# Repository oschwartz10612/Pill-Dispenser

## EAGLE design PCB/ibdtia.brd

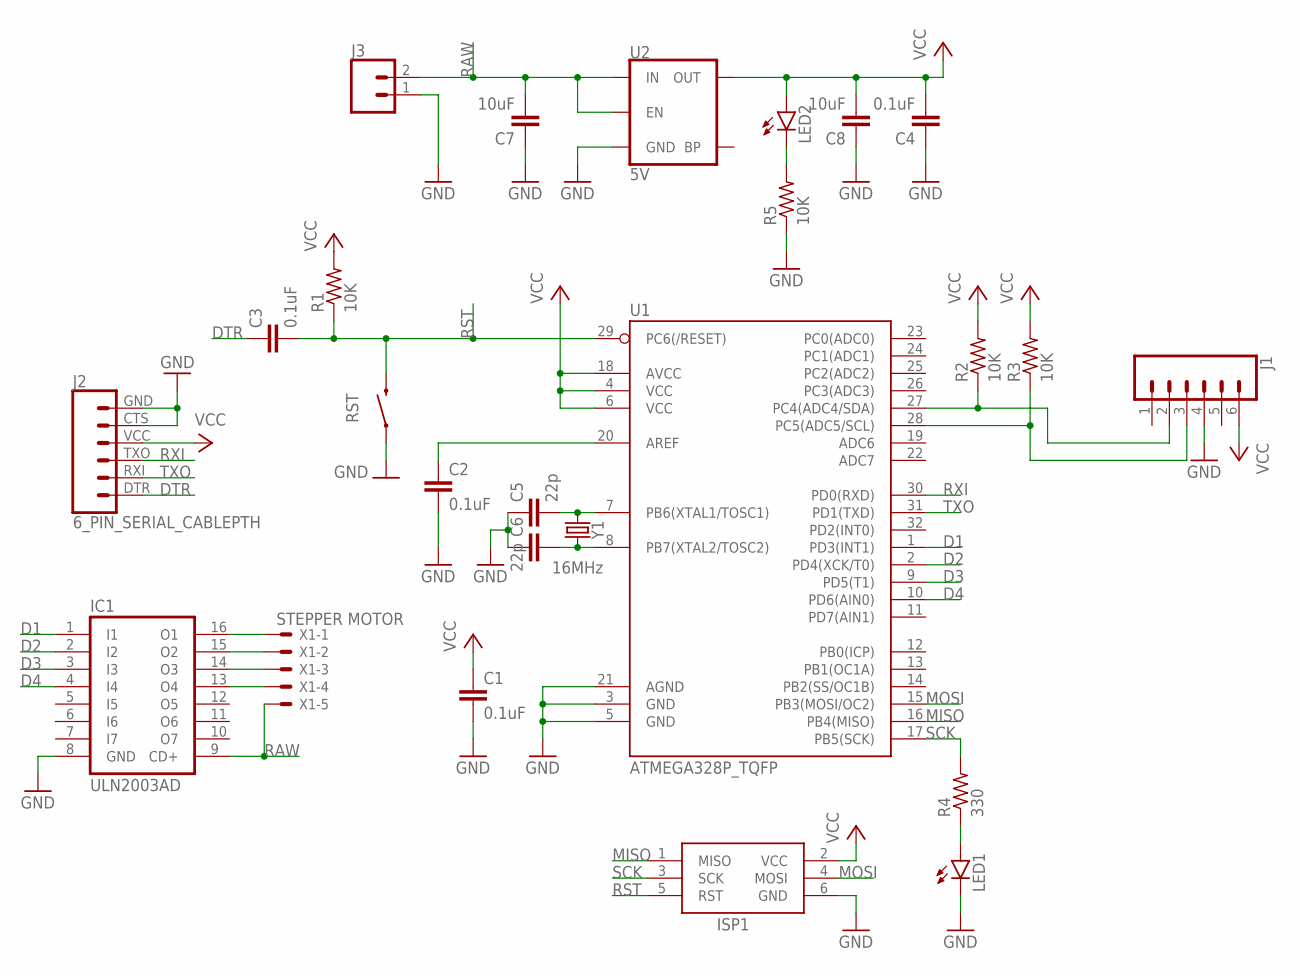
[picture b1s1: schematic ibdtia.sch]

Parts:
C1, C2, C3, C4: 0.1uF; C0805
C5, C6: 22p; C0805
C7, C8: 10uF; C0805
IC1: ULN2003AD; SO16
ISP1: AVRISP-6; AVRISP
J1: CONN_06NO_SILK_FEMALE_PTH; 1X06_NO_SILK
J2: 6_PIN_SERIAL_CABLEPTH; FTDI_BASIC
J3: CONN_02; 1X02
LED1, LED2: LEDCHIP-LED0805; CHIP-LED0805
R1, R2, R3, R5: 10K; R0805
R4: 330; R0805
RST: MOMENTARY-SWITCH-SPST-SMD-4.5MM; TACTILE_SWITCH_SMD_4.5MM
U1: ATMEGA328P_TQFP; TQFP32-08
U2: 5V; SOT23-5
X1: STEPPER MOTOR; JST-XH-05-PACKAGE-ROUND-PAD
Y1: 16MHz; CRYSTAL-SMD-5X3.2-4PAD

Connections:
D1: IC1.1 (I1), U1.1 (PD3(INT1))
D2: IC1.2 (I2), U1.2 (PD4(XCK/T0))
D3: IC1.3 (I3), U1.9 (PD5(T1))
D4: IC1.4 (I4), U1.10 (PD6(AIN0))
DTR: C3.1, J2.DTR (1)
GND: C1.2, C2.2, C4.1, C5.1, C6.1, C7.1, C8.1, IC1.8 (GND), ISP1.6 (GND), J1.4, J2.CTS (5), J2.GND (6), J3.1, LED1.C, R5.1, RST.2 (1), RST.3 (1), U1.3 (GND), U1.5 (GND), U1.21 (AGND), U2.2 (GND)
MISO: ISP1.1 (MISO), U1.16 (PB4(MISO))
MOSI: ISP1.4 (MOSI), U1.15 (PB3(MOSI/OC2))
unnamed: IC1.16 (O1), X1.1
unnamed: C5.2, U1.7 (PB6(XTAL1/TOSC1)), Y1.1
unnamed: C2.1, U1.20 (AREF)
unnamed: C6.2, U1.8 (PB7(XTAL2/TOSC2)), Y1.3 (2)
unnamed: J1.2, R2.1, U1.27 (PC4(ADC4/SDA))
unnamed: J1.3, R3.1, U1.28 (PC5(ADC5/SCL))
unnamed: IC1.15 (O2), X1.2
unnamed: LED1.A, R4.1
unnamed: IC1.14 (O3), X1.3
unnamed: IC1.13 (O4), X1.4
unnamed: LED2.C, R5.2
RAW: C7.2, IC1.9 (CD+), J3.2, U2.1 (IN), U2.3 (EN), X1.5
RST: C3.2, ISP1.5 (RST), R1.1, RST.1 (2), RST.4 (2), U1.29 (PC6(/RESET))
RXI: J2.TXO (3), U1.30 (PD0(RXD))
SCK: ISP1.3 (SCK), R4.2, U1.17 (PB5(SCK))
TXO: J2.RXI (2), U1.31 (PD1(TXD))
VCC: C1.1, C4.2, C8.2, ISP1.2 (VCC), J1.6, J2.VCC (4), LED2.A, R1.2, R2.2, R3.2, U1.4 (VCC), U1.6 (VCC), U1.18 (AVCC), U2.5 (OUT)

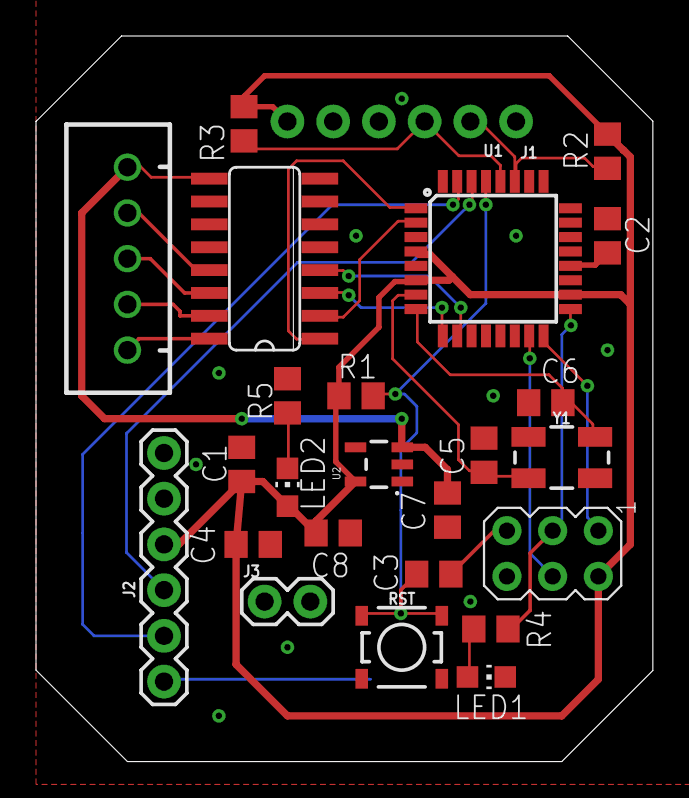
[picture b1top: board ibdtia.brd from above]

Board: 2 copper layers, 34.3 x 40.3 mm, 25 parts (0 on the bottom side), 25 nets.

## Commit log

2020-01-31 Create main.cpp
    Basic test stepper code added
2020-01-31 Added Libraries and Intiaized sensor
    Initialized PlatformIO and installed Adafruit Library
    Added sensor iltializeation to main.cpp
2020-02-01 Prepared for inital upload
    Added required dependancies
    Tested FTDI upload
    Compile successfully
2020-02-05 Activation and Finialization
    Added refernce proximity measurement and comparison to deturmine when to
    activate stepper
2020-02-12 Adjusted rotations to plate holes
2020-07-27 Add PCB files

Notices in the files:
parts and their libraries:
SparkFun-IC-Microcontroller: Licensing: Creative Commons ShareAlike 4.0 International - https://creativecommons.org/licenses/by-sa/4.0
